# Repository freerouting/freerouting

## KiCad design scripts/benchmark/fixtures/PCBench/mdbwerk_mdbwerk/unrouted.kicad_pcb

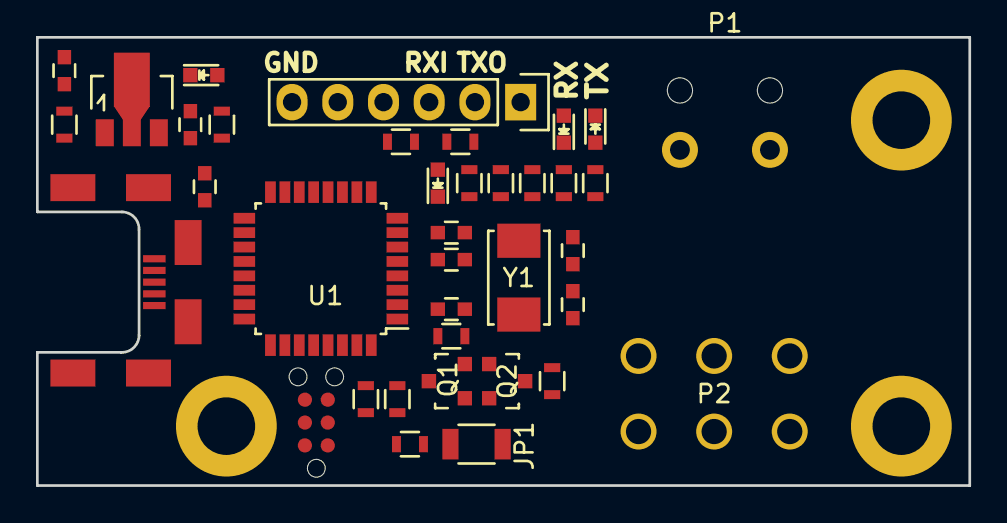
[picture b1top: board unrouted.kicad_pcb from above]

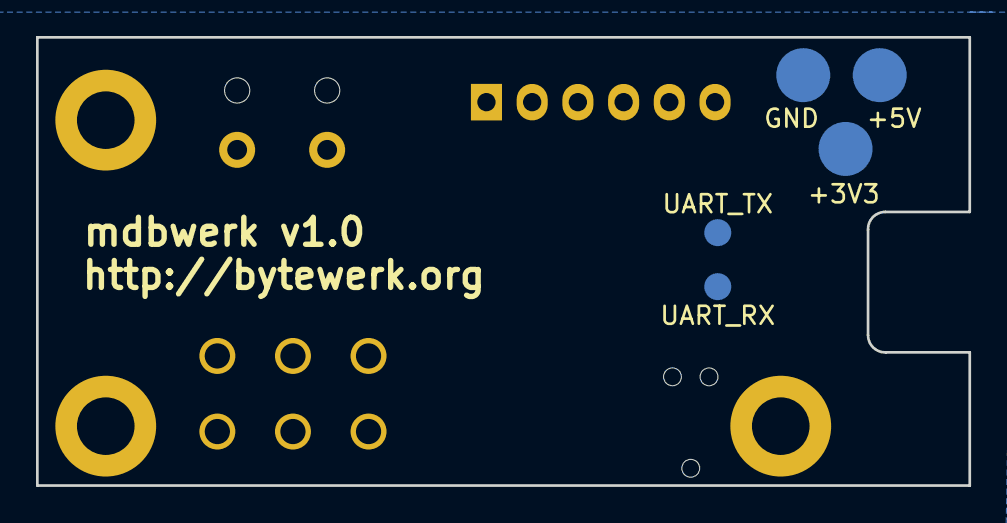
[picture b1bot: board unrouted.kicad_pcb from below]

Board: 2 copper layers, 51.8 x 24.9 mm, 42 parts (5 on the bottom side), 29 nets, no tracks yet.

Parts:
C1, C2, C3, C6: 100nF; C_0603
C4, C5: 18pF; C_0603
C7, C8: 1uF; C_0603
D1, D4: red; LED_0603
D2: yellow; LED_0603
D3: green; LED_0603
JP1: Jumper_NO_Small; R_1206
P1: CONN_01X02; TE-282836-2
P2: CONN_02X03; Molex-39-28-1063
Q1, Q2: MMBT2907; SOT-23
R1, R2, R3, R6, R7, R9, R10: 1K; R_0603
R4, R5: 10K; R_0603
R8: 10R; R_0603
R11: R; R_0603
R12: 0R; R_0603
R13, R14: 100R; R_0603
U1: STM32F042K6Tx; LQFP-32_7x7mm_Pitch0.8mm
U2: MCP1754ST-3302E/MB; SOT89-3_Housing
W1: +5V; Measurement_Point_Round-SMD-Pad_Big
W2: GND; Measurement_Point_Round-SMD-Pad_Big
W3: UART_TX; Measurement_Point_Round-SMD-Pad_Small
W4: UART_RX; Measurement_Point_Round-SMD-Pad_Small
W5: +3V3; Measurement_Point_Round-SMD-Pad_Big
X1: USB; Molex-Micro-USB-B-Middle-Mount
X2: UART; Pin_Header_Straight_1x06
X4: JTAG; TC2030-NL
Y1: 8MHz; ABM3

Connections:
5V_USB: R12.2, X1.1
+3V3: C1.1, C2.1, C3.1, C8.1, JP1.1, R1.1, R2.1, U1.1, U1.5, U1.17, U2.3, W5.1, X4.1
+5V: C7.1, D3.2, Q1.2, R3.1, R6.1, R8.1, R12.1, U2.1, W1.1
+36V: P1.2, P2.1
GND: C1.2, C2.2, C3.2, C4.2, C5.2, C6.2, C7.2, C8.2, D1.1, D4.1, P2.6, R9.2, R11.2, U1.16, U1.32, U2.2, W2.1, X1.5, X1.6, X2.6, X4.3
GNDPWR: P1.1, P2.2
MDB_RXI: P2.4, R5.1, R6.2, R7.2
MDB_TXO: P2.5, Q2.3, R9.1, R10.1
NRST: C6.1, U1.4, X4.5
unnamed: C4.1, U1.2, Y1.1
unnamed: C5.1, U1.3, Y1.2
unnamed: D1.2, R1.2
unnamed: D2.1, U1.6
unnamed: D2.2, R2.2
unnamed: D3.1, R7.1
unnamed: D4.2, R10.2
unnamed: JP1.2, R11.1, U1.31
unnamed: Q1.1, Q2.2, R8.2
unnamed: Q1.3, Q2.1, R4.1
unnamed: R13.1, X2.2
unnamed: R14.1, X2.3
SWCLK: U1.24, X4.2
SWDIO: U1.23, X4.4
USART1_RX: R5.2, U1.20, W4.1
USART1_TX: R3.2, R4.2, U1.19, W3.1
USART2_RX: R14.2, U1.9
USART2_TX: R13.2, U1.8
USB_DM: U1.21, X1.2
USB_DP: U1.22, X1.3

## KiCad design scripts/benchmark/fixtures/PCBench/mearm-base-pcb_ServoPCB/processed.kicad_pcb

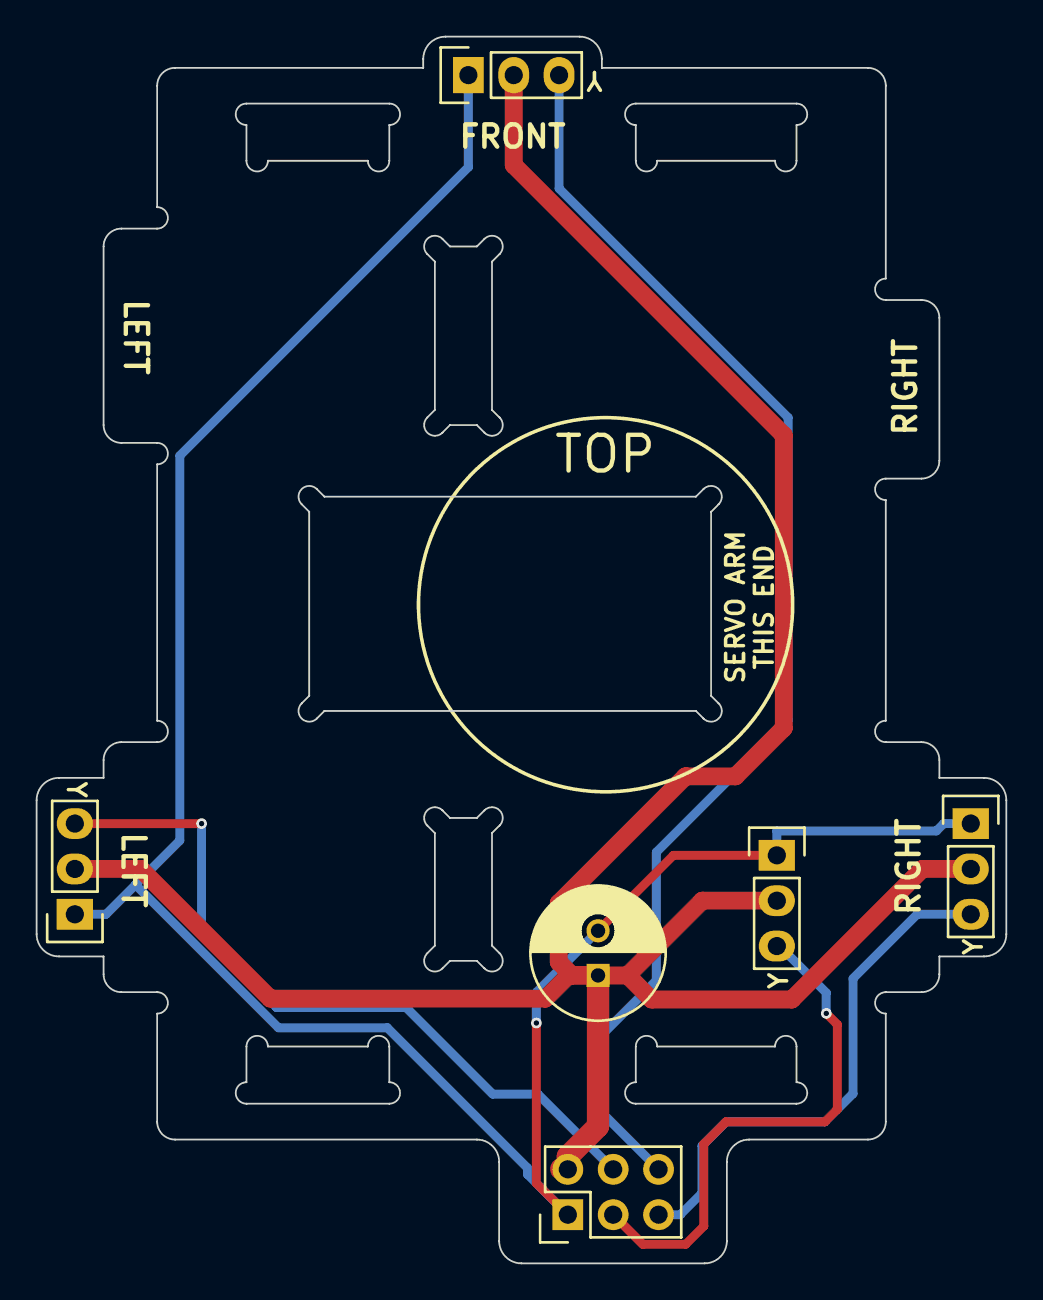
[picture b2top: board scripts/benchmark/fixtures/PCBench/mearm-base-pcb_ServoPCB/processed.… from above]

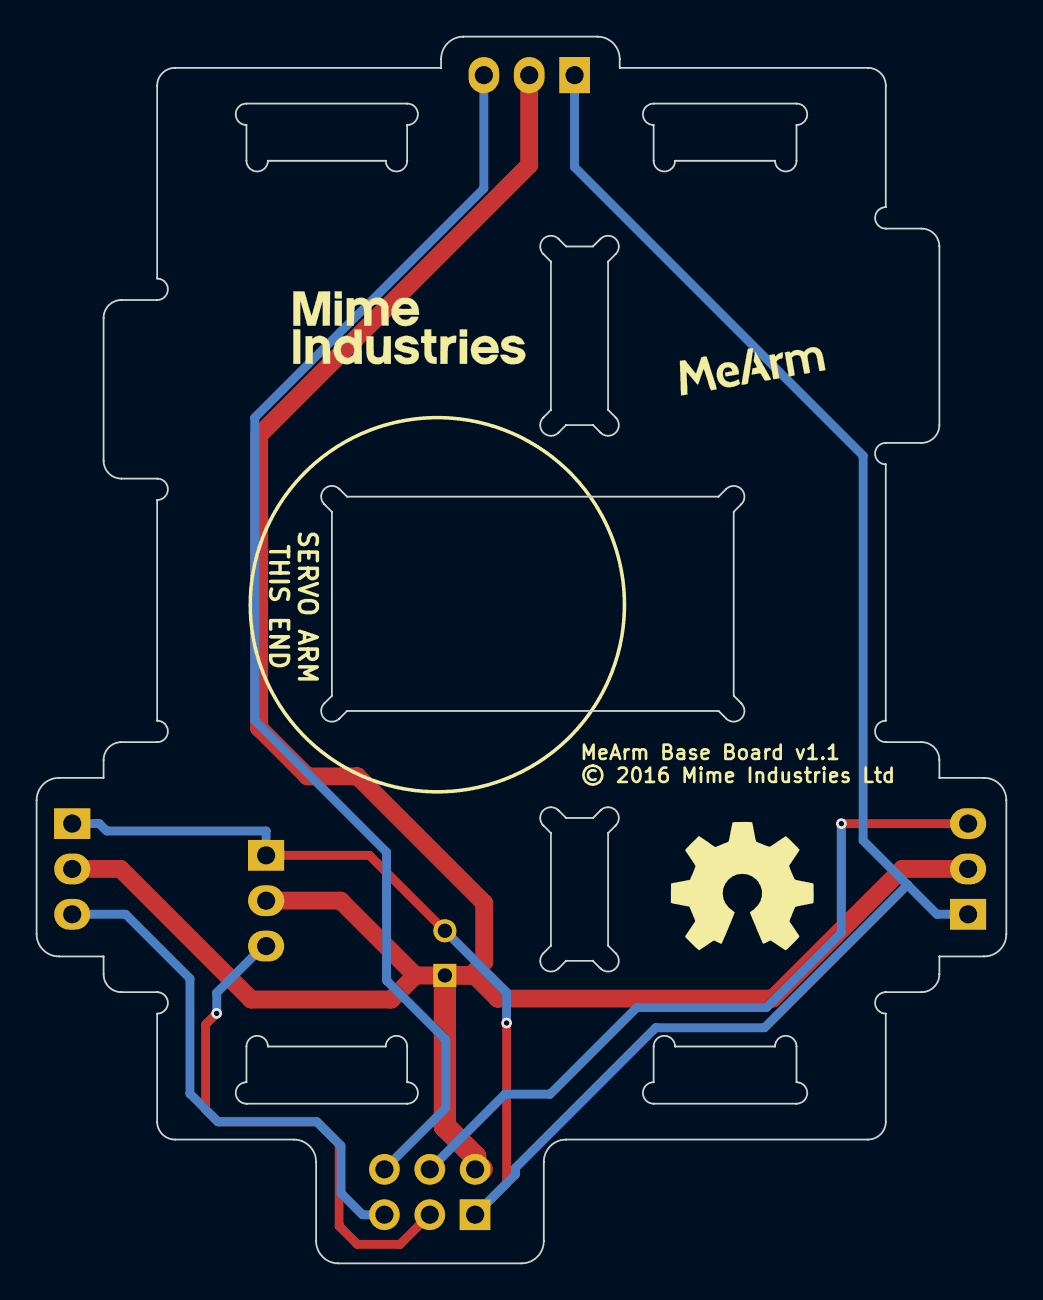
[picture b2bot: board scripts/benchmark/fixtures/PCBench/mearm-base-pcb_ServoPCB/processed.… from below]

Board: 2 copper layers, 54.3 x 68.7 mm, 9 parts (3 on the bottom side), 6 nets.

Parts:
ART1: OSHW-LOGO; OSHW_LOGO
ART2: LOGO; MIME_LOGO
ART3: LOGO; MEARM_LOGO
C1: CP; C_Radial_D7.5_L11.2_P2.5
P1: CONNECTOR; Pin_Header_Straight_2x03
P2: BASE_SERVO; Pin_Header_Straight_1x03
P3: LEFT_SERVO; Pin_Header_Straight_1x03
P4: RIGHT_SERVO; Pin_Header_Straight_1x03
P5: GRIP_SERVO; Pin_Header_Straight_1x03

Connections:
GND: C1.2, P1.1, P2.1, P3.1, P4.1, P5.1
unnamed: P1.3, P2.3
unnamed: P1.4, P3.3
unnamed: P1.5, P4.3
unnamed: P1.6, P5.3
VCC: C1.1, P1.2, P2.2, P3.2, P4.2, P5.2

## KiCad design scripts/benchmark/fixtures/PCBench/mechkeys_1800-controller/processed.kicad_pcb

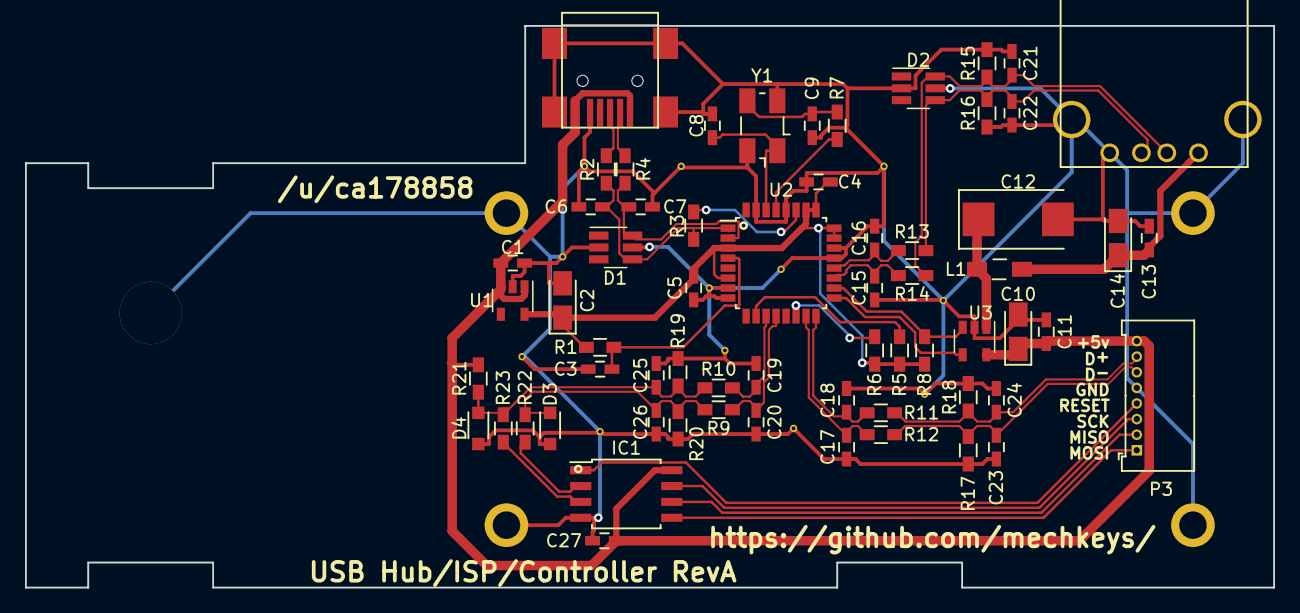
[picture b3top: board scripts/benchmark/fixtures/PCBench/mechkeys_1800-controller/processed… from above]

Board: 2 copper layers, 100.0 x 45.0 mm, 63 parts (0 on the bottom side), 36 nets.

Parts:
C1, C3: 1µF; C_0603_HandSoldering
C2, C10: 4.7µF; Tantalum_Case-S_EIA-3216-12_Reflow
C4, C11, C27: 0.1µF; C_0603_HandSoldering
C5, C13: 0.01µF; C_0603_HandSoldering
C6, C7: 20pF; C_0603_HandSoldering
C8, C9: C; C_0603_HandSoldering
C12: 220µF; Tantalum_Case-X_EIA-7343-43_Reflow
C14: 47µF; Tantalum_Case-S_EIA-3216-12_Reflow
C15, C16, C17, C18, C19, C20: 22pF; C_0603_HandSoldering
C21, C22, C23, C24, C25, C26: 47pF; C_0603_HandSoldering
D1, D2: SN65220; SOT-23-6_Handsoldering
D3, D4: D_Zener; SOD-323_HandSoldering
IC1: ATTINY45-S; SOIJ-8_5.3x5.3mm_Pitch1.27mm
L1: Ferrite_Bead_Small; Choke_SMD_1206_Standard
P1: USB_OTG; USB_Mini-B
P2: USB_A
P3: CONN_01X08; Molex_PicoBlade_53048-0810_08x1.25mm_Angled
R1, R5, R6, R8, R15, R16, R17, R18, R19, R20: 15k; R_0603_HandSoldering
R2, R4, R9, R10, R11, R12, R13, R14: 30; R_0603_HandSoldering
R3: 1.5k; R_0603_HandSoldering
R7: R; R_0603_HandSoldering
R21: 1.7k; R_0603_HandSoldering
R22, R23: 68; R_0603_HandSoldering
U1: TPS76333; SOT-23-5
U2: TUSB2036; LQFP-32_7x7mm_Pitch0.8mm
U3: TPS2041B; SOT-23-5
Y1: Crystal_GND3; Crystal_SMD_5032_4Pads

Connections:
+3V3: C2.1, C4.1, C5.1, R1.2, R5.1, R6.1, R8.2, U1.5, U2.3, U2.6, U2.23, U2.24, U2.25, U2.26
+5V: C1.1, C10.1, C11.1, C27.1, IC1.8, P1.1, P3.8, R21.2, U1.1, U1.3, U3.5
D0+: C6.1, D1.4, R2.1, R3.2, U2.1
D0-: C7.1, D1.6, R4.1, U2.2
D1+: C20.1, R9.1, U2.12
D1-: C19.1, R10.1, U2.11
D1D+: C26.1, D3.1, R9.2, R20.1, R22.1
D1D-: C25.1, D4.1, R10.2, R19.1, R21.1, R23.1
D2+: C18.1, R11.1, U2.16
D2-: C17.1, R12.1, U2.15
D2D+: C24.1, P3.7, R11.2, R18.1
D2D-: C23.1, P3.6, R12.2, R17.1
D3+: C16.1, R13.1, U2.20
D3-: C15.1, R14.1, U2.19
D3D+: C22.1, D2.4, P2.3, R13.2, R16.1
D3D-: C21.1, D2.6, P2.2, R14.2, R15.1
D+: P1.3, R2.2
D-: P1.2, R4.2
GND: C1.2, C2.2, C3.2, C4.2, C5.2, C6.2, C7.2, C8.2, C9.2, C10.2, C11.2, C12.2, C13.2, C14.2, C15.2, C16.2, C17.2, C18.2, C19.2, C20.2, C21.2, C22.2, C23.2, C24.2, C25.2, C26.2, C27.2, D1.2, D1.5, D2.2, D2.5, D3.2, D4.2, IC1.4, P1.5, P1.6, P2.4, P2.5, P3.5, R15.2, R16.2, R17.2, R18.2, R19.2, R20.2, U1.2, U2.7, U2.8, U2.21, U2.22, U2.28, U2.31, U3.2, Y1.3
MISO: IC1.6, P3.2
MOSI: IC1.5, P3.1
unnamed: C8.1, U2.30, Y1.1
unnamed: C9.1, R7.2, Y1.2
unnamed: C12.1, L1.2, U3.1
unnamed: IC1.2, R22.2
unnamed: IC1.3, R23.2
unnamed: R3.1, U2.27
unnamed: R5.2, U2.10
unnamed: R6.2, U2.14
unnamed: R7.1, U2.29
OVRCUR3: R8.1, U2.18, U3.3
PWRON3: U2.17, U3.4
RESET: IC1.1, P3.4
RST: C3.1, R1.1, U2.4
SCK: IC1.7, P3.3
VBUS3: C13.1, C14.1, L1.1, P2.1

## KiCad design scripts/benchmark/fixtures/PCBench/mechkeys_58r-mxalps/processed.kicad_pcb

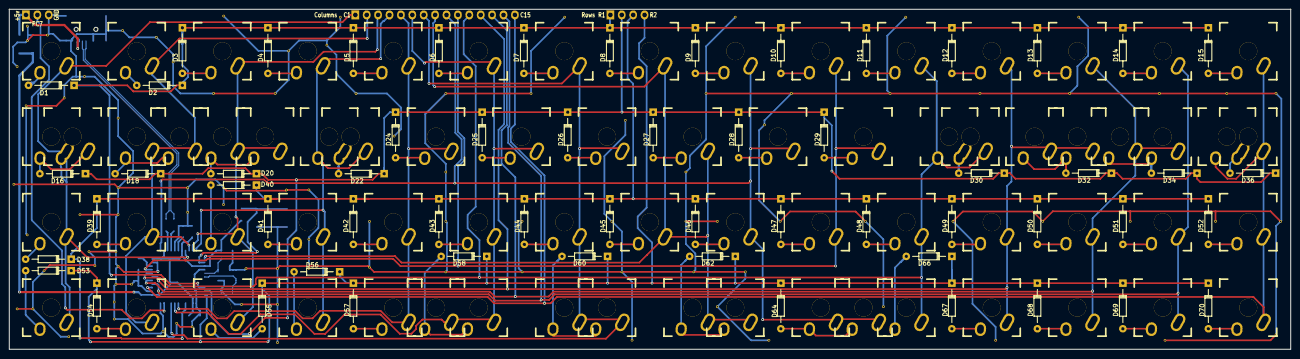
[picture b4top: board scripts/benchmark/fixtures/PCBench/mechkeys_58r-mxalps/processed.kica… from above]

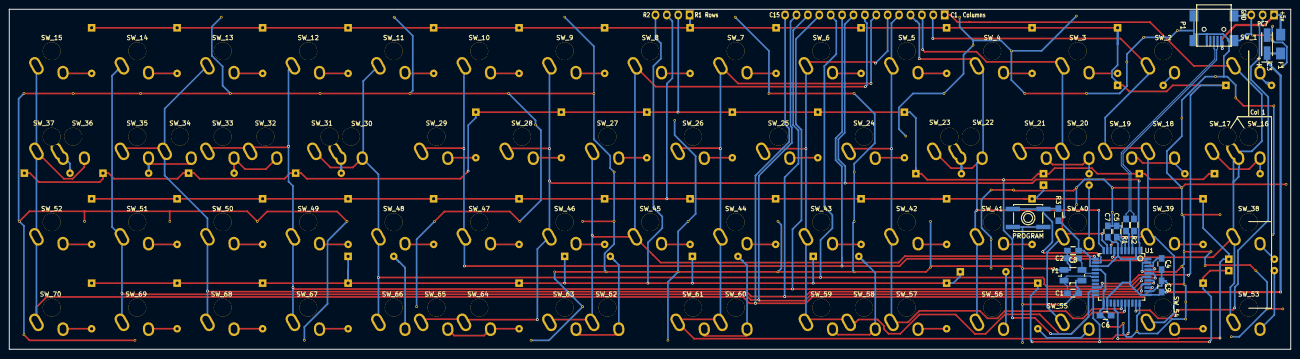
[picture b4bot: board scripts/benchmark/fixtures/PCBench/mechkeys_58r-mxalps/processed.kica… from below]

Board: 2 copper layers, 285.5 x 75.8 mm, 148 parts (17 on the bottom side), 90 nets.

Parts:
C1, C2, C4, C6, C7, C8, C9: C_Small; C_0805_HandSoldering
C3: CP_Small; TantalC_SizeA_EIA-3216_HandSoldering
C5: 1µF; C_0805_HandSoldering
D1, D2, D3, D4, D5, D6, D7, D8, D9, D10, D11, D12, D13, D14, D15, D16, D18, D20, D22, D24, D25, D26, D27, D28, D29, D30, D32, D34, D36, D38, D39, D40, D41, D42, D43, D44, D45, D46, D47, D48, D49, D50, D51, D52, D53, D54, D55, D56, D57, D58, D60, D62, D64, D66, D67, D68, D69, D70: D; Diode_DO-35_SOD27_Horizontal_RM10
F1: F_Small; Fuse_SMD1206_HandSoldering
P1: USB_OTG; USB_Mini-B
P2: CONN_01X03; Socket_Strip_Straight_1x03_NoOverlay
P3: CONN_01X15; Socket_Strip_Straight_1x15_NoOverlay
P4: CONN_01X04; Socket_Strip_Straight_1x04_NoOverlay
PROGRAM: SW_PUSH; SW_SPST_EVQP0
R1, R2: 22; R_0805_HandSoldering
R3: 10k; R_0805_HandSoldering
SW_1, SW_2, SW_3, SW_4, SW_5, SW_6, SW_7, SW_8, SW_9, SW_10, SW_11, SW_12, SW_13, SW_14, SW_15, SW_16, SW_17, SW_18, SW_19, SW_20, SW_21, SW_22, SW_23, SW_24, SW_25, SW_26, SW_27, SW_28, SW_29, SW_30, SW_31, SW_32, SW_33, SW_34, SW_35, SW_36, SW_37, SW_38, SW_39, SW_40, SW_41, SW_42, SW_43, SW_44, SW_45, SW_46, SW_47, SW_48, SW_49, SW_50, SW_51, SW_52, SW_53, SW_54, SW_55, SW_56, SW_57, SW_58, SW_59, SW_60, SW_61, SW_62, SW_63, SW_64, SW_65, SW_66, SW_67, SW_68, SW_69, SW_70: MX_LED; MXALPS-NOLED
U1: ATmega32U4; LQFP-44_10x10mm_Pitch0.8mm
Y1: Crystal_Small; Crystal_SMD_5032_4Pads

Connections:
+5V: C3.1, C6.1, C7.1, C8.1, C9.1, F1.2, R3.2, U1.2, U1.7, U1.14, U1.24, U1.34, U1.44
C1: P3.1, SW_1.SW1, SW_16.SW1, SW_17.SW2, SW_38.SW1, SW_53.SW1, U1.8
C2: P3.2, SW_2.SW1, SW_18.SW1, SW_19.SW1, SW_39.SW1, SW_54.SW1, U1.9
C3: P3.3, SW_3.SW1, SW_20.SW1, SW_21.SW1, SW_40.SW1, SW_55.SW1, U1.10
C4: P3.4, SW_4.SW1, SW_22.SW2, SW_23.SW1, SW_41.SW1, SW_56.SW1, U1.11
C5: P3.5, SW_5.SW1, SW_24.SW1, SW_42.SW1, SW_57.SW1, U1.28
C6: P3.6, SW_6.SW1, SW_25.SW1, SW_43.SW1, SW_58.SW1, SW_59.SW1, U1.29
C7: P3.7, SW_7.SW1, SW_26.SW1, SW_44.SW1, SW_60.SW1, SW_61.SW1, U1.30
C8: P3.8, SW_8.SW1, SW_27.SW1, SW_45.SW1, SW_62.SW1, SW_63.SW1, U1.12
C9: P3.9, SW_9.SW1, SW_28.SW1, SW_46.SW1, SW_64.SW1, SW_65.SW1, U1.1
C10: P3.10, SW_10.SW1, SW_29.SW1, SW_47.SW1, U1.41
C11: P3.11, SW_11.SW1, SW_30.SW2, SW_31.SW1, SW_48.SW1, SW_66.SW1, U1.40
C12: P3.12, SW_12.SW1, SW_32.SW1, SW_33.SW1, SW_49.SW1, SW_67.SW1, U1.39
C13: P3.13, SW_13.SW1, SW_34.SW1, SW_35.SW1, SW_50.SW1, SW_68.SW1, U1.38
C14: P3.14, SW_14.SW1, SW_51.SW1, SW_69.SW1, U1.37
C15: P3.15, SW_15.SW1, SW_36.SW2, SW_37.SW1, SW_52.SW1, SW_70.SW1, U1.36
D+: R1.1, U1.4
D-: R2.1, U1.3
GND: C1.1, C2.2, C3.2, C4.2, C5.2, C6.2, C7.2, C8.2, C9.2, P1.5, P1.6, P2.3, PROGRAM.1, U1.5, U1.15, U1.23, U1.33, U1.35, U1.43, Y1.3
unnamed: C1.2, U1.17, Y1.1
unnamed: C2.1, U1.16, Y1.2
unnamed: C4.1, U1.42
unnamed: C5.1, U1.6
unnamed: D1.2, SW_1.SW2
unnamed: D2.2, SW_2.SW2
unnamed: D3.2, SW_3.SW2
unnamed: D4.2, SW_4.SW2
unnamed: D5.2, SW_5.SW2
unnamed: D6.2, SW_6.SW2
unnamed: D7.2, SW_7.SW2
unnamed: D8.2, SW_8.SW2
unnamed: D9.2, SW_9.SW2
unnamed: D10.2, SW_10.SW2
unnamed: D11.2, SW_11.SW2
unnamed: D12.2, SW_12.SW2
unnamed: D13.2, SW_13.SW2
unnamed: D14.2, SW_14.SW2
unnamed: D15.2, SW_15.SW2
unnamed: D16.2, SW_16.SW2, SW_17.SW1
unnamed: D18.2, SW_18.SW2, SW_19.SW2
unnamed: D20.2, SW_20.SW2, SW_21.SW2
unnamed: D22.2, SW_22.SW1, SW_23.SW2
unnamed: D24.2, SW_24.SW2
unnamed: D25.2, SW_25.SW2
unnamed: D26.2, SW_26.SW2
unnamed: D27.2, SW_27.SW2
unnamed: D28.2, SW_28.SW2
unnamed: D29.2, SW_29.SW2
unnamed: D30.2, SW_30.SW1, SW_31.SW2
unnamed: D32.2, SW_32.SW2, SW_33.SW2
unnamed: D34.2, SW_34.SW2, SW_35.SW2
unnamed: D36.2, SW_36.SW1, SW_37.SW2
unnamed: D38.2, SW_38.SW2
unnamed: D39.2, SW_39.SW2
unnamed: D40.2, SW_40.SW2
unnamed: D41.2, SW_41.SW2
unnamed: D42.2, SW_42.SW2
unnamed: D43.2, SW_43.SW2
unnamed: D44.2, SW_44.SW2
unnamed: D45.2, SW_45.SW2
unnamed: D46.2, SW_46.SW2
unnamed: D47.2, SW_47.SW2
unnamed: D48.2, SW_48.SW2
unnamed: D49.2, SW_49.SW2
unnamed: D50.2, SW_50.SW2
unnamed: D51.2, SW_51.SW2
unnamed: D52.2, SW_52.SW2
unnamed: D53.2, SW_53.SW2
unnamed: D54.2, SW_54.SW2
unnamed: D55.2, SW_55.SW2
unnamed: D56.2, SW_56.SW2
unnamed: D57.2, SW_57.SW2
unnamed: D58.2, SW_58.SW2, SW_59.SW2
unnamed: D60.2, SW_60.SW2, SW_61.SW2
unnamed: D62.2, SW_62.SW2, SW_63.SW2
unnamed: D64.2, SW_64.SW2, SW_65.SW2
unnamed: D66.2, SW_66.SW2
unnamed: D67.2, SW_67.SW2
unnamed: D68.2, SW_68.SW2
unnamed: D69.2, SW_69.SW2
unnamed: D70.2, SW_70.SW2
unnamed: PROGRAM.2, R3.1, U1.13
PC7: P2.2, U1.32
R1: D1.1, D2.1, D3.1, D4.1, D5.1, D6.1, D7.1, D8.1, D9.1, D10.1, D11.1, D12.1, D13.1, D14.1, D15.1, P4.1, U1.20
R2: D16.1, D18.1, D20.1, D22.1, D24.1, D25.1, D26.1, D27.1, D28.1, D29.1, D30.1, D32.1, D34.1, D36.1, P4.2, U1.21
R3: D38.1, D39.1, D40.1, D41.1, D42.1, D43.1, D44.1, D45.1, D46.1, D47.1, D48.1, D49.1, D50.1, D51.1, D52.1, P4.3, U1.26
R4: D53.1, D54.1, D55.1, D56.1, D57.1, D58.1, D60.1, D62.1, D64.1, D66.1, D67.1, D68.1, D69.1, D70.1, P4.4, U1.22
USB+: P1.3, R1.2
USB-: P1.2, R2.2
VUSB: F1.1, P1.1, P2.1

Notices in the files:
scripts/benchmark/fixtures/PCBench/mearm-base-pcb_ServoPCB/processed.kicad_pcb:
© 2016 Mime Industries Ltd
